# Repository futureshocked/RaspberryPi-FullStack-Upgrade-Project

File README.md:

# Raspberry Pi Full Stack Upgrade Project

This is the repository for Raspberry Pi Full Stack Upgrade Project, a course from [Tech Explorations](https://techexplorations.com).

[Learn more about this course](https://techexplorations.com/so/rpifs_up).

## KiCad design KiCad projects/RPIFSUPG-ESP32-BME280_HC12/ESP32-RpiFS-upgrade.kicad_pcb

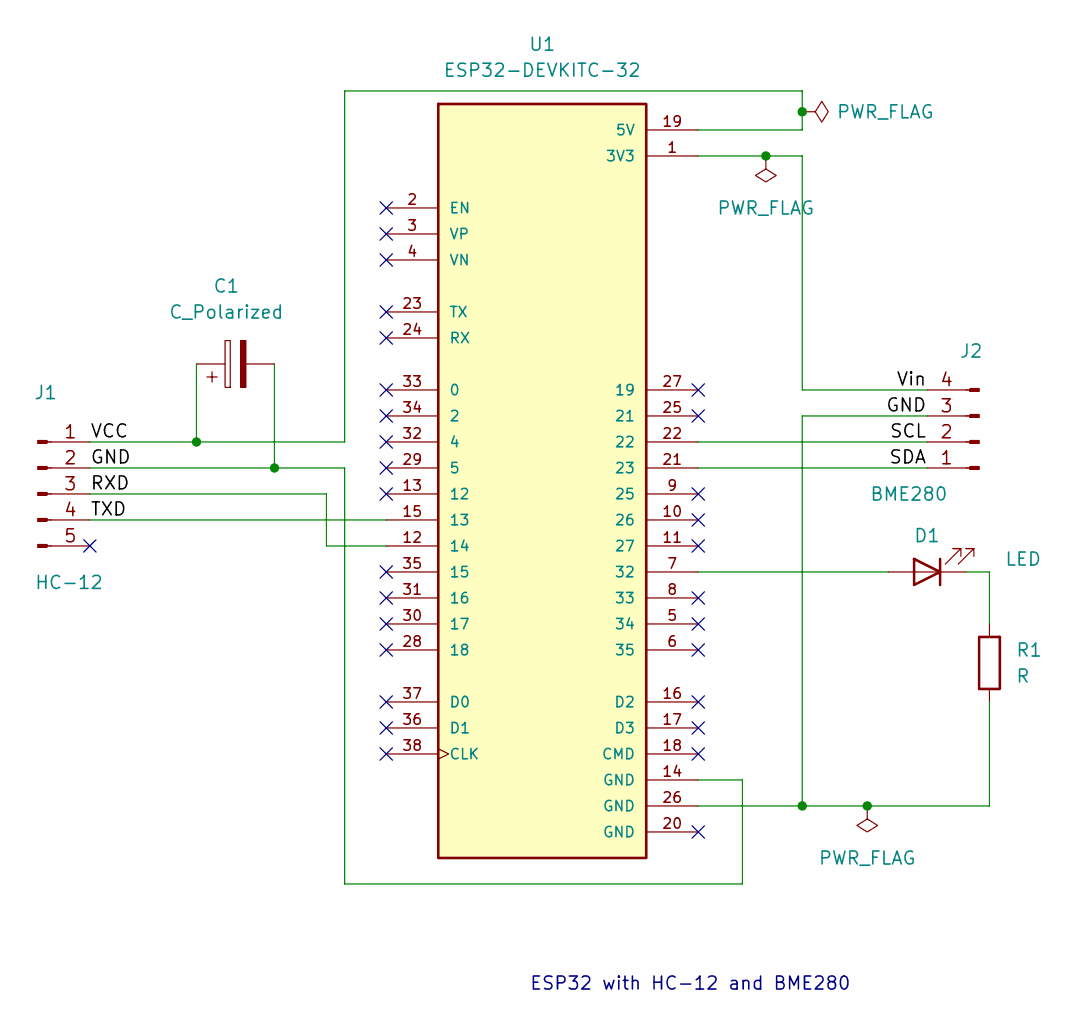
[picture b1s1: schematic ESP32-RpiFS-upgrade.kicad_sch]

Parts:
C1: C_Polarized; C_0805_2012Metric_Pad1.18x1.45mm_HandSolder
D1: LED; LED_0805_2012Metric_Pad1.15x1.40mm_HandSolder
J1: HC-12; PinHeader_1x05_P2.54mm_Vertical
J2: BME280; PinHeader_1x04_P2.54mm_Vertical
R1: R; R_0805_2012Metric_Pad1.20x1.40mm_HandSolder
U1: ESP32-DEVKITC-32; ESPRESSIF_ESP32-DEVKITC-32UE; PARTREV V4

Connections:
/GND: C1.2, J1.2, J2.3, R1.1, U1.14 (GND), U1.26 (GND)
/RXD: J1.3, U1.12 (14)
/SCL: J2.2, U1.22
/SDA: J2.1, U1.21 (23)
/TXD: J1.4, U1.15 (13)
/VCC: C1.1, J1.1, U1.19 (5V)
/Vin: J2.4, U1.1 (3V3)
unnamed: D1.1 (K), R1.2
unnamed: D1.2 (A), U1.7 (32)

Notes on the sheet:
ESP32 with HC-12 and BME280

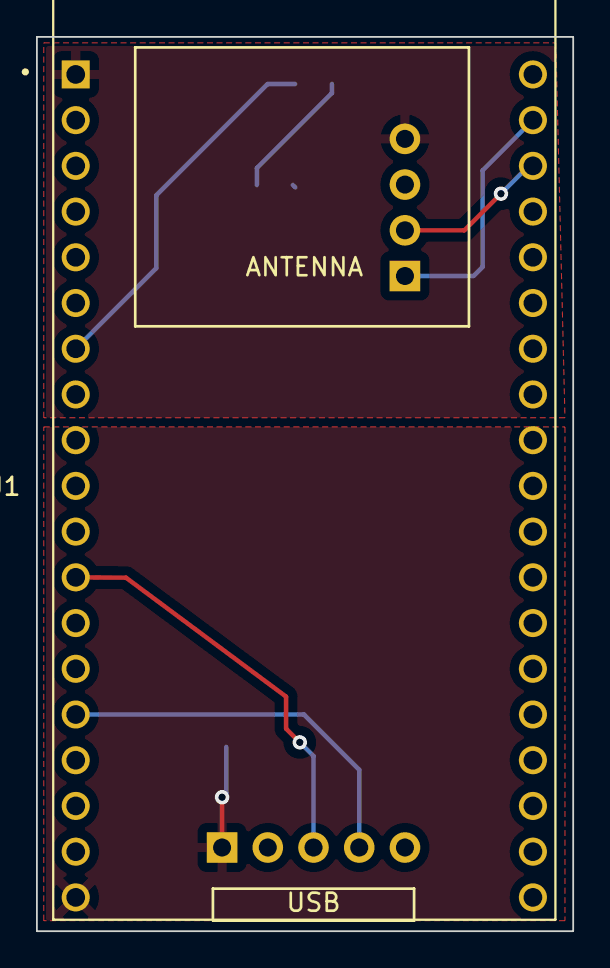
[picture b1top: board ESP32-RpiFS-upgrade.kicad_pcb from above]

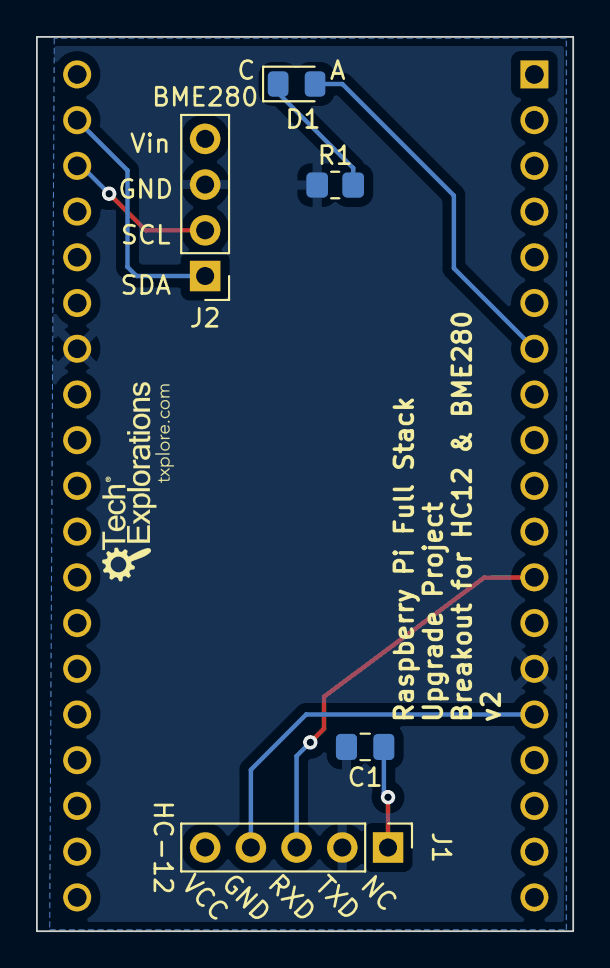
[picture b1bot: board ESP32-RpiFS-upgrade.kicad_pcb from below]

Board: 2 copper layers, 29.8 x 49.7 mm, 6 parts (5 on the bottom side), 9 nets.

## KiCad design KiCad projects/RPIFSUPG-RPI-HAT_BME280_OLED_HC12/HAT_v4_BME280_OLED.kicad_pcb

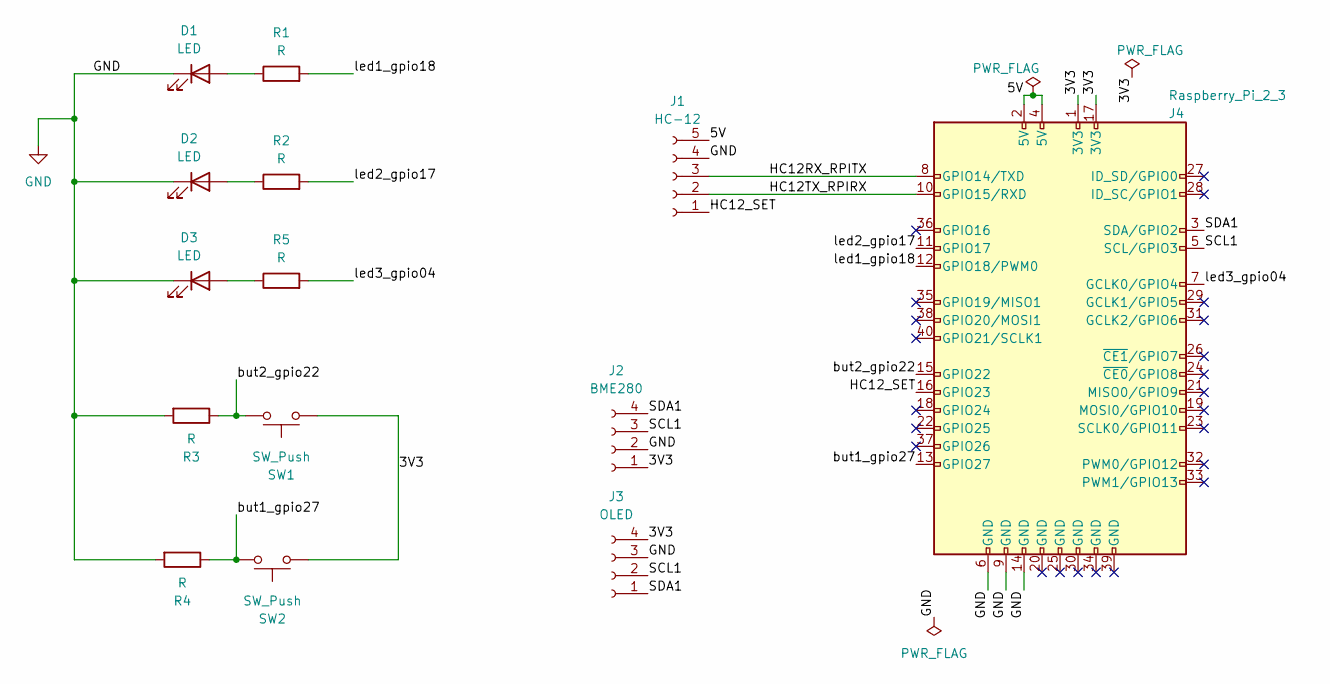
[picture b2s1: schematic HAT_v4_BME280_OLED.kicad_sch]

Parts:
D1, D2, D3: LED; LED_0805_2012Metric
J1: HC-12; PinSocket_1x05_P2.54mm_Vertical
J2: BME280; PinSocket_1x04_P2.54mm_Vertical
J3: OLED; PinSocket_1x04_P2.54mm_Vertical
J4: Raspberry_Pi_2_3; PinSocket_2x09_P2.54mm_Vertical
R1, R2, R3, R4, R5: R; R_0805_2012Metric
SW1, SW2: SW_Push; SW_PUSH_6mm_H4.3mm

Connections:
/3V3: J2.1, J3.4, J4.1 (3V3), J4.17 (3V3), SW1.1, SW2.1
/5V: J1.5, J4.2 (5V), J4.4 (5V)
/HC12RX_RPITX: J1.3, J4.8 (GPIO14/TXD)
/HC12TX_RPIRX: J1.2, J4.10 (GPIO15/RXD)
/HC12_SET: J1.1, J4.16 (GPIO23)
/SCL1: J2.3, J3.2, J4.5 (SCL/GPIO3)
/SDA1: J2.4, J3.1, J4.3 (SDA/GPIO2)
/but1_gpio27: J4.13 (GPIO27), R4.1, SW2.2
/but2_gpio22: J4.15 (GPIO22), R3.1, SW1.2
/led1_gpio18: J4.12 (GPIO18/PWM0), R1.2
/led2_gpio17: J4.11 (GPIO17), R2.2
/led3_gpio04: J4.7 (GCLK0/GPIO4), R5.2
GND: D1.1 (K), D2.1 (K), D3.1 (K), J1.4, J2.2, J3.3, J4.6 (GND), J4.9 (GND), J4.14 (GND), R3.2, R4.2
unnamed: D1.2 (A), R1.1
unnamed: D2.2 (A), R2.1
unnamed: D3.2 (A), R5.1

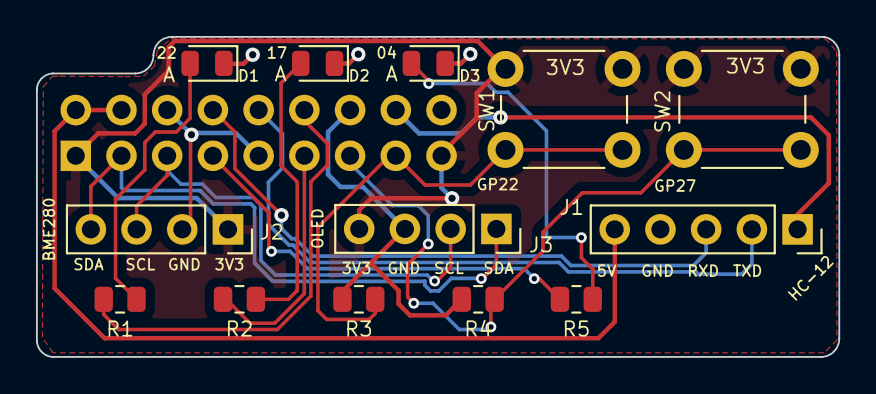
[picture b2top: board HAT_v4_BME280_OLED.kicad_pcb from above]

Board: 2 copper layers, 44.6 x 17.8 mm, 14 parts (1 on the bottom side), 16 nets.

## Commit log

2022-11-02 First commit.
2022-11-02 Added ESP32 code.
2022-11-07 Added completed hardware schematics.
2022-11-07 Added demos folder.
2022-11-07 Added misc files.
2022-11-08 Added uwsgi configration for lecture 7.80
2022-11-08 Added systemd service configuration for lecture 7.100.
2022-11-08 Added ESP32 sketch for lecture 8.80
2022-11-12 Fixed orientation of headers.
2022-11-14 Added esp32 sketch with comms verification.
2023-01-20 Uncommented pressure SQL query
